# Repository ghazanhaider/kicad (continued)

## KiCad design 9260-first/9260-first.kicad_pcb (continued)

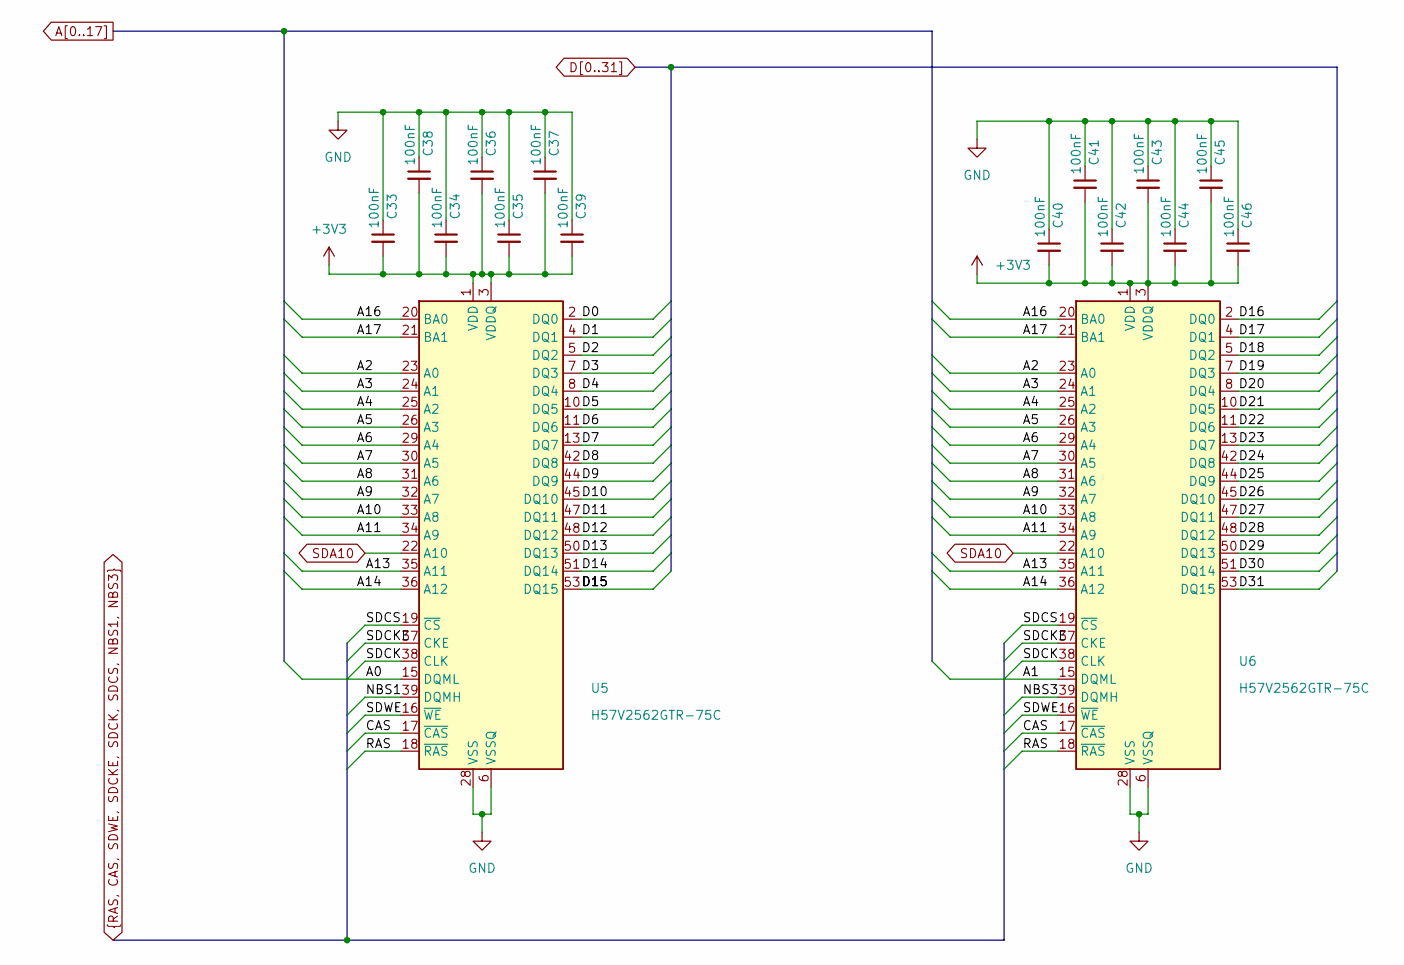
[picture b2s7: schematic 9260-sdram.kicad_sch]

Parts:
C33, C34, C35, C36, C37, C38, C39, C40, C41, C42, C43, C44, C45, C46: 100nF; C_0805_2012Metric
U5, U6: H57V2562GTR-75C; TSOP-II-54_22.2x10.16mm_P0.8mm

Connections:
3V3: C33.2, C34.2, C35.2, C36.2, C37.2, C38.2, C39.2, C40.2, C41.2, C42.2, C43.2, C44.2, C45.2, C46.2, U5.1 (VDD), U5.3 (VDDQ), U5.9 (VDDQ), U5.14 (VDD), U5.27 (VDD), U5.43 (VDDQ), U5.49 (VDDQ), U6.1 (VDD), U6.3 (VDDQ), U6.9 (VDDQ), U6.14 (VDD), U6.27 (VDD), U6.43 (VDDQ), U6.49 (VDDQ); also elsewhere on the board
A0: U5.15 (DQML); also elsewhere on the board
A1: U6.15 (DQML); also elsewhere on the board
A2: U5.23 (A0), U6.23 (A0); also elsewhere on the board
A3: U5.24 (A1), U6.24 (A1); also elsewhere on the board
A4: U5.25 (A2), U6.25 (A2); also elsewhere on the board
A5: U5.26 (A3), U6.26 (A3); also elsewhere on the board
A6: U5.29 (A4), U6.29 (A4); also elsewhere on the board
A7: U5.30 (A5), U6.30 (A5); also elsewhere on the board
A8: U5.31 (A6), U6.31 (A6); also elsewhere on the board
A9: U5.32 (A7), U6.32 (A7); also elsewhere on the board
A10: U5.33 (A8), U6.33 (A8); also elsewhere on the board
A11: U5.34 (A9), U6.34 (A9); also elsewhere on the board
A13: U5.35 (A11), U6.35 (A11); also elsewhere on the board
A14: U5.36 (A12), U6.36 (A12); also elsewhere on the board
A16: U5.20 (BA0), U6.20 (BA0); also elsewhere on the board
A17: U5.21 (BA1), U6.21 (BA1); also elsewhere on the board
CAS: U5.17 (~CAS), U6.17 (~CAS); also elsewhere on the board
D0: U5.2 (DQ0); also elsewhere on the board
D1: U5.4 (DQ1); also elsewhere on the board
D2: U5.5 (DQ2); also elsewhere on the board
D3: U5.7 (DQ3); also elsewhere on the board
D4: U5.8 (DQ4); also elsewhere on the board
D5: U5.10 (DQ5); also elsewhere on the board
D6: U5.11 (DQ6); also elsewhere on the board
D7: U5.13 (DQ7); also elsewhere on the board
D8: U5.42 (DQ8); also elsewhere on the board
D9: U5.44 (DQ9); also elsewhere on the board
D10: U5.45 (DQ10); also elsewhere on the board
D11: U5.47 (DQ11); also elsewhere on the board
D12: U5.48 (DQ12); also elsewhere on the board
D13: U5.50 (DQ13); also elsewhere on the board
D14: U5.51 (DQ14); also elsewhere on the board
D15: U5.53 (DQ15); also elsewhere on the board
D16: U6.2 (DQ0); also elsewhere on the board
D17: U6.4 (DQ1); also elsewhere on the board
D18: U6.5 (DQ2); also elsewhere on the board
D19: U6.7 (DQ3); also elsewhere on the board
D20: U6.8 (DQ4); also elsewhere on the board
D21: U6.10 (DQ5); also elsewhere on the board
D22: U6.11 (DQ6); also elsewhere on the board
D23: U6.13 (DQ7); also elsewhere on the board
D24: U6.42 (DQ8); also elsewhere on the board
D25: U6.44 (DQ9); also elsewhere on the board
D26: U6.45 (DQ10); also elsewhere on the board
D27: U6.47 (DQ11); also elsewhere on the board
D28: U6.48 (DQ12); also elsewhere on the board
D29: U6.50 (DQ13); also elsewhere on the board
D30: U6.51 (DQ14); also elsewhere on the board
D31: U6.53 (DQ15); also elsewhere on the board
GND: C33.1, C34.1, C35.1, C36.1, C37.1, C38.1, C39.1, C40.1, C41.1, C42.1, C43.1, C44.1, C45.1, C46.1, U5.6 (VSSQ), U5.12 (VSSQ), U5.28 (VSS), U5.41 (VSS), U5.46 (VSSQ), U5.52 (VSSQ), U5.54 (VSS), U6.6 (VSSQ), U6.12 (VSSQ), U6.28 (VSS), U6.41 (VSS), U6.46 (VSSQ), U6.52 (VSSQ), U6.54 (VSS); also elsewhere on the board
NBS1: U5.39 (DQMH); also elsewhere on the board
NBS3: U6.39 (DQMH); also elsewhere on the board
RAS: U5.18 (~RAS), U6.18 (~RAS); also elsewhere on the board
SDA10: U5.22 (A10), U6.22 (A10); also elsewhere on the board
SDCK: U5.38 (CLK), U6.38 (CLK); also elsewhere on the board
SDCKE: U5.37 (CKE), U6.37 (CKE); also elsewhere on the board
SDCS: U5.19 (~CS), U6.19 (~CS); also elsewhere on the board
SDWE: U5.16 (~WE), U6.16 (~WE); also elsewhere on the board

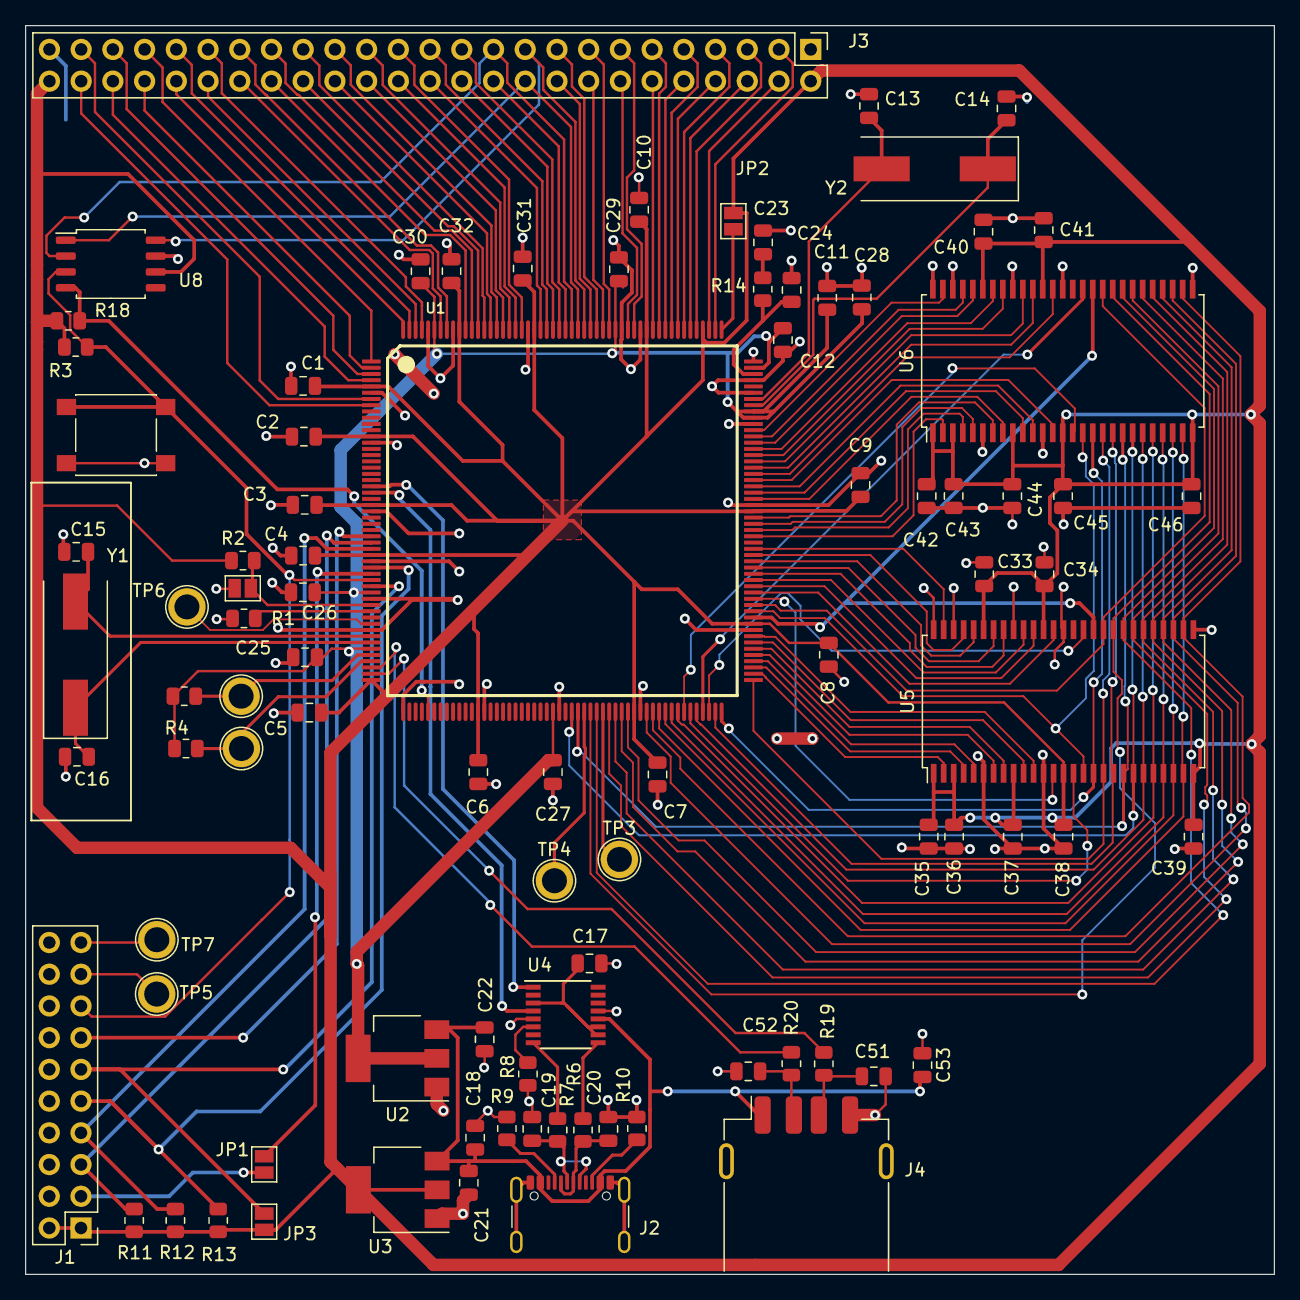
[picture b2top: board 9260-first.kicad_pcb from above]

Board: 2 copper layers, 100.0 x 100.0 mm, 91 parts (0 on the bottom side), 146 nets.

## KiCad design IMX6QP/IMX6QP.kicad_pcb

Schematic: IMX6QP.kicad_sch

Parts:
U1: MCIMX6QP5EYM; BGA-624_21x21mm_Layout25x25_P0.8mm

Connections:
GND: U1.A5 (FA_ANA), U1.B5 (VDD_FA), U1.E12 (TEST_MODE); also elsewhere on the board

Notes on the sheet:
UNUSED PINS Label overrides

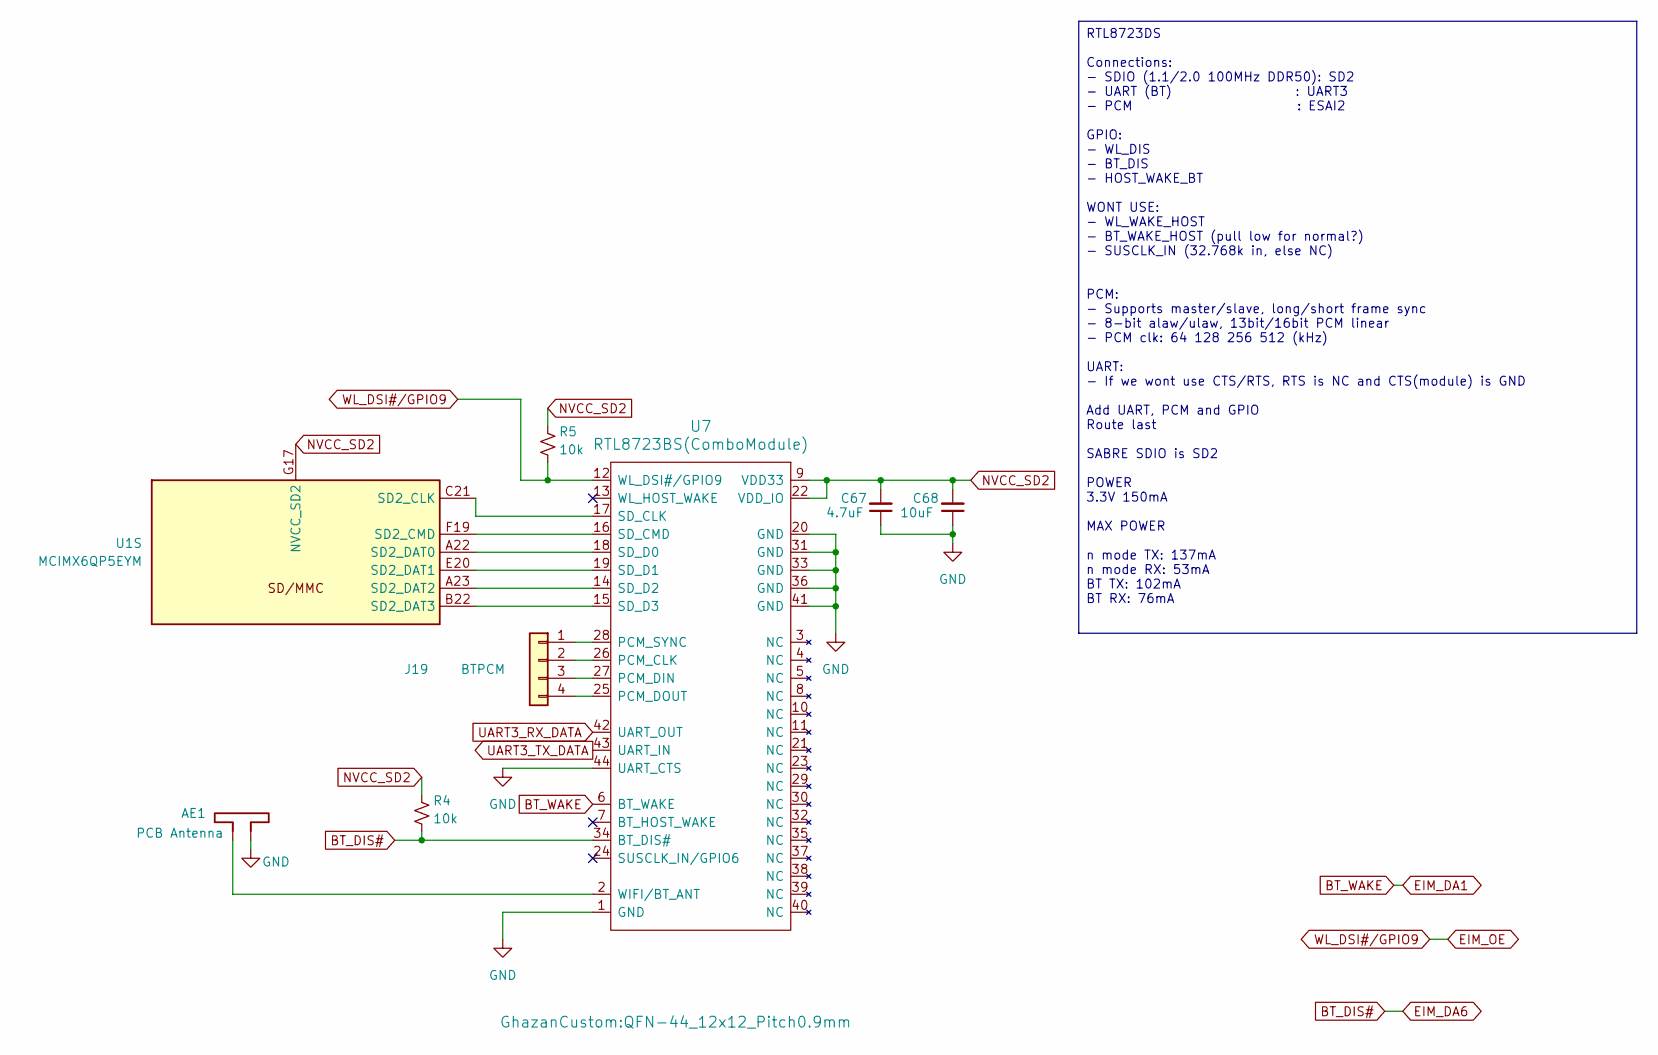
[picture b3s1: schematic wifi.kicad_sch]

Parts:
AE1: PCB Antenna; Texas_SWRA117D_2.4GHz_Left
C67: 4.7uF; C_0603_1608Metric
C68: 10uF; C_0603_1608Metric
J19: BTPCM; PinHeader_1x04_P2.54mm_Vertical
R4, R5: 10k; R_0603_1608Metric
U1: MCIMX6QP5EYM; BGA-624_21x21mm_Layout25x25_P0.8mm
U7: RTL8723BS(ComboModule); QFN-44_12x12_Pitch0.9mm

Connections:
3V3_SW2: C67.2, C68.2, R4.1, R5.1, U1.G17 (NVCC_SD2), U7.9 (VDD33), U7.22 (VDD_IO); also elsewhere on the board
BT_DIS#: R4.2, U7.34 (BT_DIS#); also elsewhere on the board
BT_WAKE: U7.6 (BT_WAKE); also elsewhere on the board
EIM_OE: R5.2, U7.12 (WL_DSI#/GPIO9); also elsewhere on the board
GND: AE1.2, C67.1, C68.1, U7.1 (GND), U7.20 (GND), U7.31 (GND), U7.33 (GND), U7.36 (GND), U7.41 (GND), U7.44 (UART_CTS); also elsewhere on the board
unnamed: J19.1, U7.28 (PCM_SYNC)
unnamed: J19.2, U7.26 (PCM_CLK)
unnamed: J19.3, U7.27 (PCM_DIN)
unnamed: J19.4, U7.25 (PCM_DOUT)
unnamed: U1.C21 (SD2_CLK), U7.17 (SD_CLK)
unnamed: U1.F19 (SD2_CMD), U7.16 (SD_CMD)
unnamed: U1.A22 (SD2_DAT0), U7.18 (SD_D0)
unnamed: U1.E20 (SD2_DAT1), U7.19 (SD_D1)
unnamed: U1.A23 (SD2_DAT2), U7.14 (SD_D2)
unnamed: U1.B22 (SD2_DAT3), U7.15 (SD_D3)
unnamed: AE1.1, U7.2 (WIFI/BT_ANT)
UART3_RX_DATA: U7.42 (UART_OUT); also elsewhere on the board
UART3_TX_DATA: U7.43 (UART_IN); also elsewhere on the board

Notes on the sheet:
RTL8723DS Connections: - SDIO (1.1/2.0 100MHz DDR50): SD2 - UART (BT) : UART3 - PCM : ESAI2 GPIO: - WL_DIS - BT_DIS - HOST_WAKE_BT WONT USE: - WL_WAKE_HOST - BT_WAKE_HOST (pull low for normal?) - SUSCLK_IN (32.768k in, else NC) PCM: - Supports master/slave, long/short frame sync - 8-bit alaw/ulaw, 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

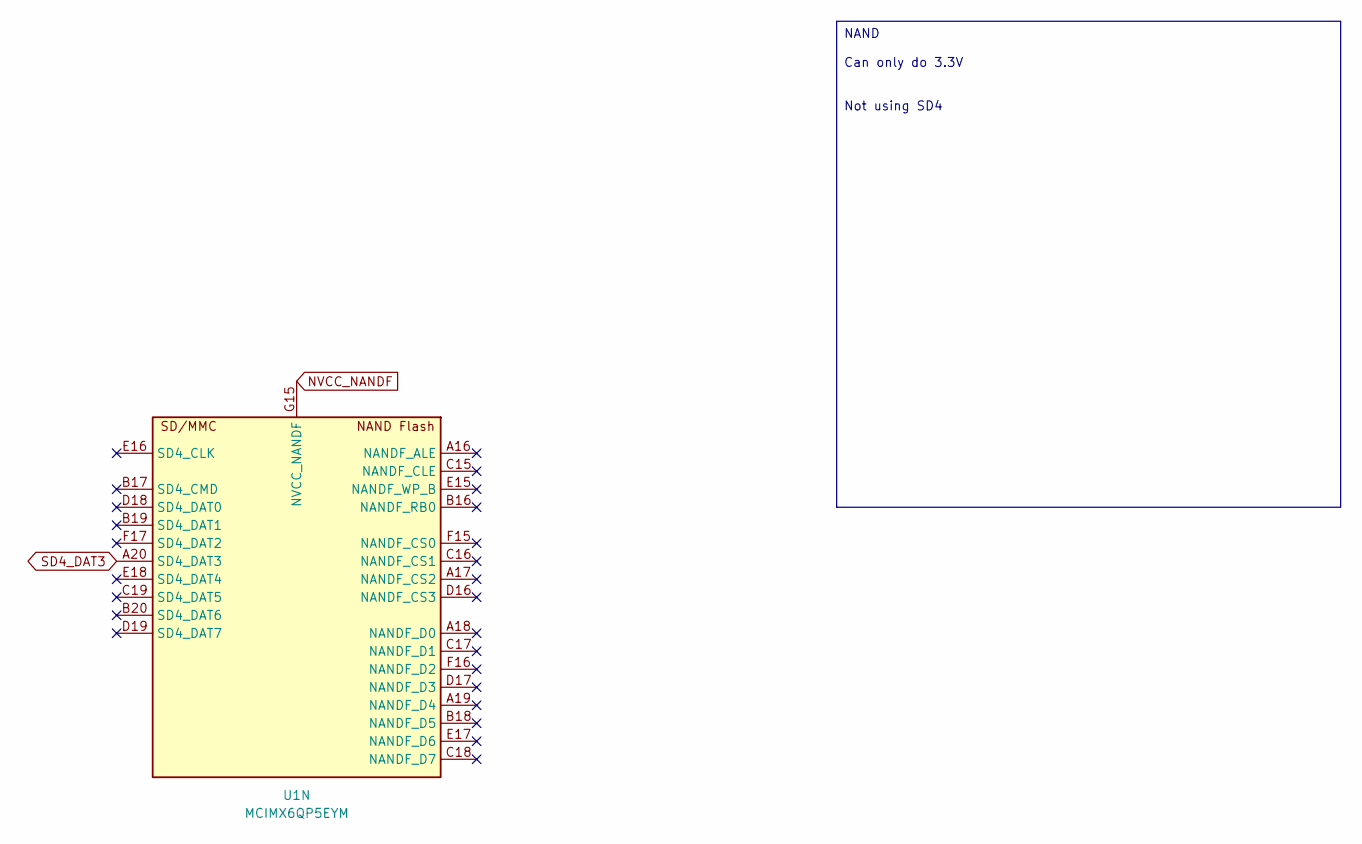
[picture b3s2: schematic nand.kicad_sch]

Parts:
U1: MCIMX6QP5EYM; BGA-624_21x21mm_Layout25x25_P0.8mm

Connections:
3V3_SW2: U1.G15 (NVCC_NANDF); also elsewhere on the board
SD1_CD: U1.A20 (SD4_DAT3); also elsewhere on the board

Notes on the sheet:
NAND Can only do 3.3V Not using SD4

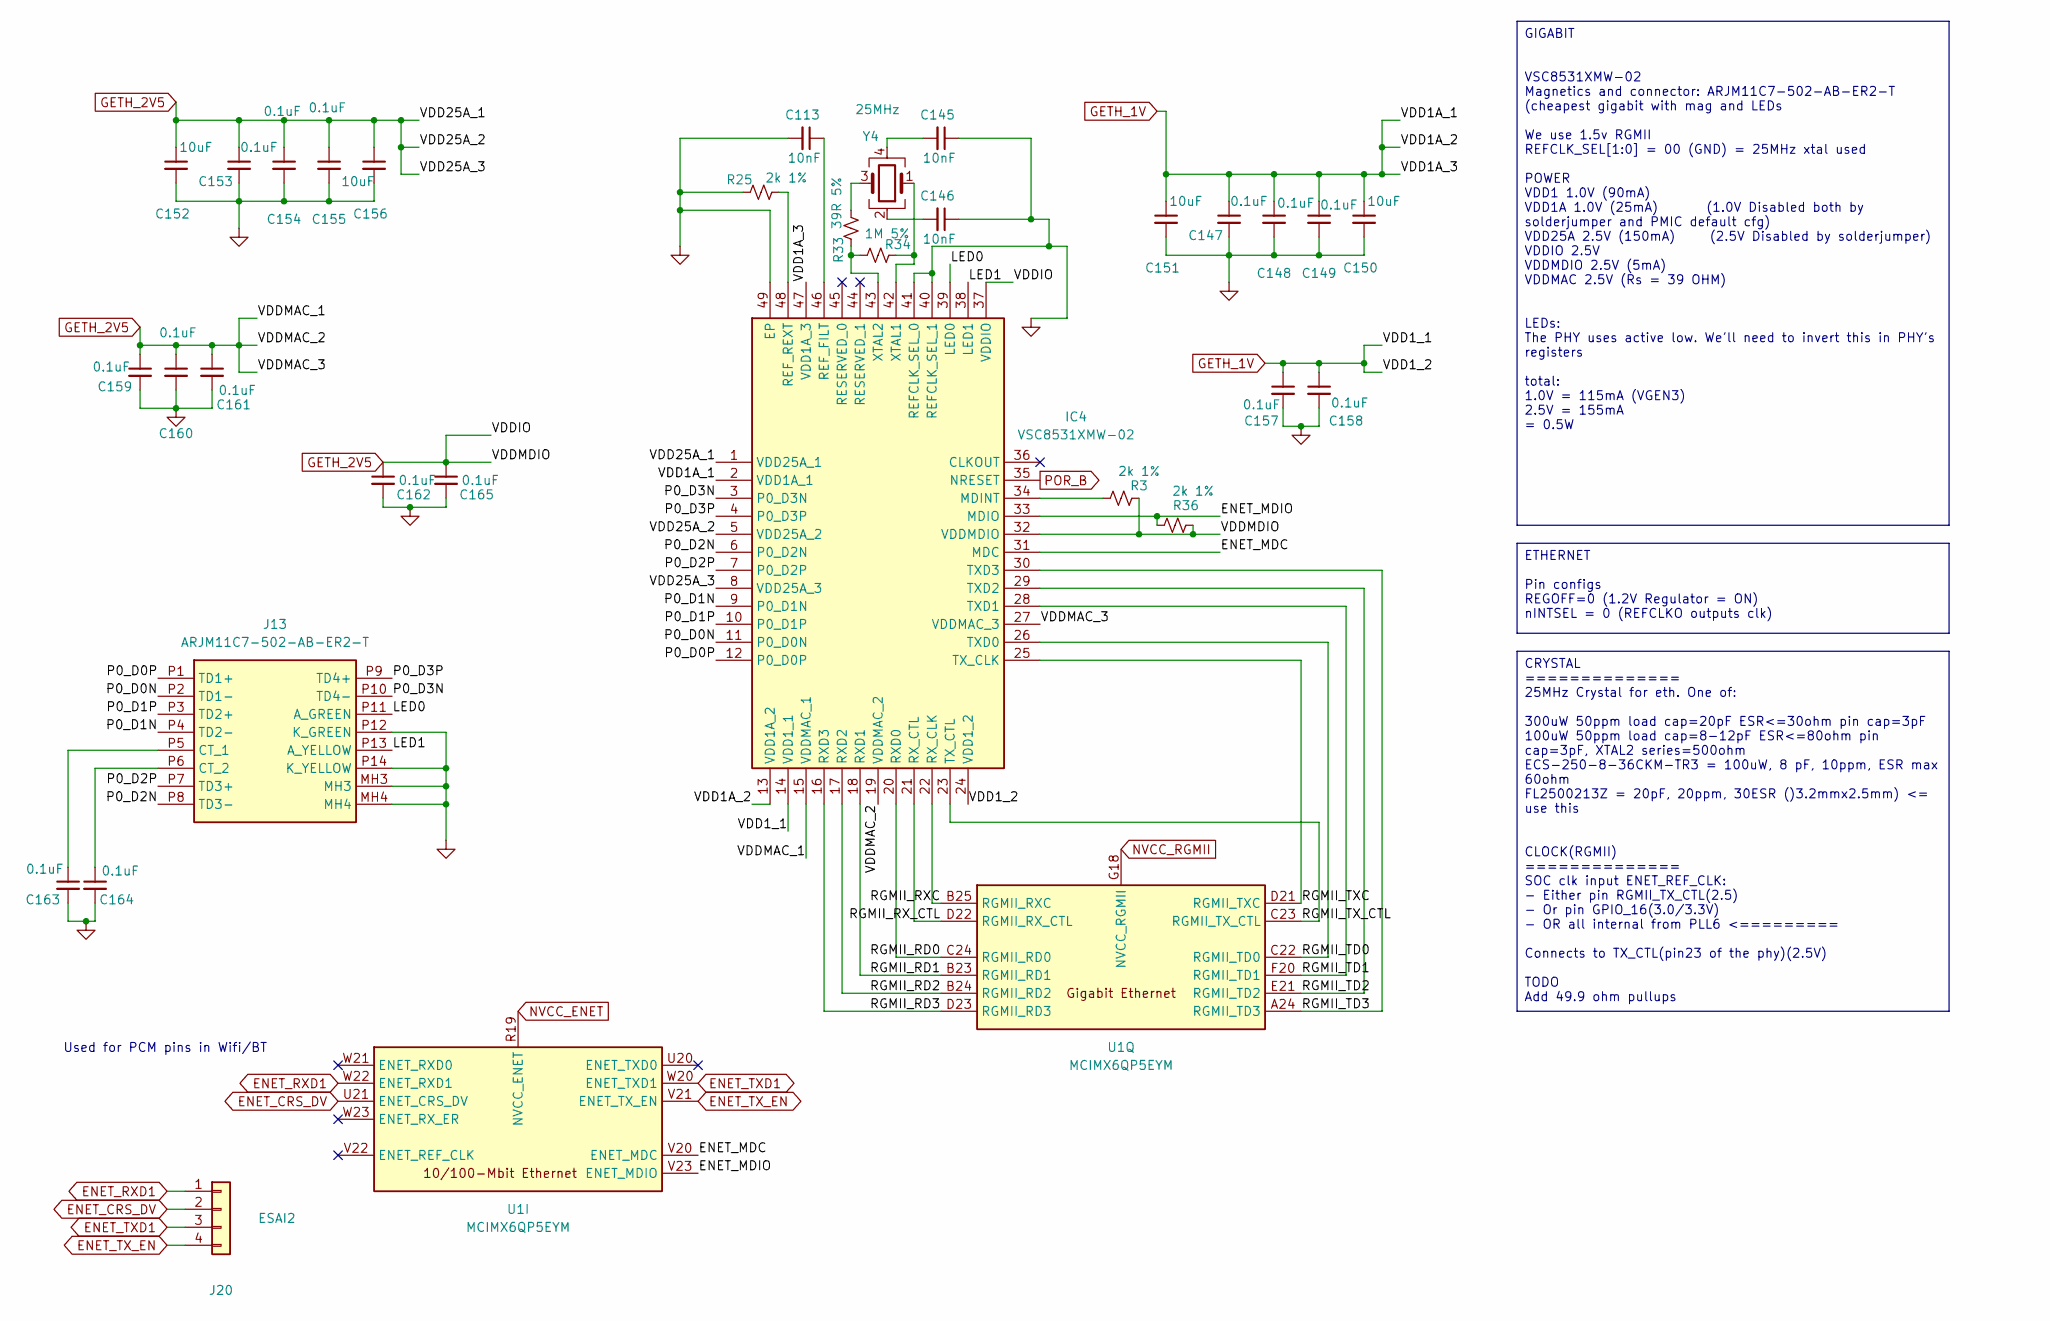
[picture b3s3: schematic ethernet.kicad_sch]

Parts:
C113, C145, C146: 10nF; C_0603_1608Metric
C147, C148, C149, C153, C154, C155, C157, C158, C159, C160, C161, C162, C163, C164, C165: 0.1uF; C_0603_1608Metric
C150, C151, C152, C156: 10uF; C_0603_1608Metric
IC4: VSC8531XMW-02; QFN40P600X600X90-49N-D; Mouser Part Number 494-VSC8531XMW-02
J13: ARJM11C7-502-AB-ER2-T; ARJM11C7502ABER2T; Mouser Part Number 815-RJM11C7502ABER2T
J20: ESAI2; PinHeader_1x04_P2.54mm_Vertical
R3, R25, R36: 2k 1%; R_0603_1608Metric
R33: 39R 5%; R_0603_1608Metric
R34: 1M 5%; R_0603_1608Metric
U1: MCIMX6QP5EYM; BGA-624_21x21mm_Layout25x25_P0.8mm
Y4: 25MHz; Crystal_SMD_3225-4Pin_3.2x2.5mm

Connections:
1V5_SW3: U1.G18 (NVCC_RGMII); also elsewhere on the board
3V3_SW2: U1.R19 (NVCC_ENET); also elsewhere on the board
/Ethernet/ENET_MDC: IC4.31 (MDC), U1.V20 (ENET_MDC)
/Ethernet/ENET_MDIO: IC4.33 (MDIO), R36.2, U1.V23 (ENET_MDIO)
/Ethernet/LED0: IC4.39 (LED0), J13.P11 (A_GREEN)
/Ethernet/LED1: IC4.38 (LED1), J13.P13 (A_YELLOW)
/Ethernet/P0_D0N: IC4.11 (P0_D0N), J13.P2 (TD1-)
/Ethernet/P0_D0P: IC4.12 (P0_D0P), J13.P1 (TD1+)
/Ethernet/P0_D1N: IC4.9 (P0_D1N), J13.P4 (TD2-)
/Ethernet/P0_D1P: IC4.10 (P0_D1P), J13.P3 (TD2+)
/Ethernet/P0_D2N: IC4.6 (P0_D2N), J13.P8 (TD3-)
/Ethernet/P0_D2P: IC4.7 (P0_D2P), J13.P7 (TD3+)
/Ethernet/P0_D3N: IC4.3 (P0_D3N), J13.P10 (TD4-)
/Ethernet/P0_D3P: IC4.4 (P0_D3P), J13.P9 (TD4+)
/Ethernet/RGMII_RD0: IC4.20 (RXD0), U1.C24 (RGMII_RD0)
/Ethernet/RGMII_RD1: IC4.18 (RXD1), U1.B23 (RGMII_RD1)
/Ethernet/RGMII_RD2: IC4.17 (RXD2), U1.B24 (RGMII_RD2)
/Ethernet/RGMII_RD3: IC4.16 (RXD3), U1.D23 (RGMII_RD3)
/Ethernet/RGMII_RXC: IC4.22 (RX_CLK), U1.B25 (RGMII_RXC)
/Ethernet/RGMII_RX_CTL: IC4.21 (RX_CTL), U1.D22 (RGMII_RX_CTL)
/Ethernet/RGMII_TD0: IC4.26 (TXD0), U1.C22 (RGMII_TD0)
/Ethernet/RGMII_TD1: IC4.28 (TXD1), U1.F20 (RGMII_TD1)
/Ethernet/RGMII_TD2: IC4.29 (TXD2), U1.E21 (RGMII_TD2)
/Ethernet/RGMII_TD3: IC4.30 (TXD3), U1.A24 (RGMII_TD3)
/Ethernet/RGMII_TXC: IC4.25 (TX_CLK), U1.D21 (RGMII_TXC)
/Ethernet/RGMII_TX_CTL: IC4.23 (TX_CTL), U1.C23 (RGMII_TX_CTL)
ENET_CRS_DV: J20.2, U1.U21 (ENET_CRS_DV)
ENET_RXD1: J20.1, U1.W22 (ENET_RXD1)
ENET_TXD1: J20.3, U1.W20 (ENET_TXD1)
ENET_TX_EN: J20.4, U1.V21 (ENET_TX_EN)
GETH_1V: C147.1, C148.1, C149.1, C150.1, C151.1, C157.1, C158.1, IC4.2 (VDD1A_1), IC4.13 (VDD1A_2), IC4.14 (VDD1_1), IC4.24 (VDD1_2), IC4.47 (VDD1A_3); also elsewhere on the board
GETH_2V5: C152.1, C153.1, C154.1, C155.1, C156.1, C159.1, C160.1, C161.1, C162.1, C165.1, IC4.1 (VDD25A_1), IC4.5 (VDD25A_2), IC4.8 (VDD25A_3), IC4.15 (VDDMAC_1), IC4.19 (VDDMAC_2), IC4.27 (VDDMAC_3), IC4.32 (VDDMDIO), IC4.37 (VDDIO), R3.1, R36.1; also elsewhere on the board
GND: C113.2, C145.1, C146.1, C147.2, C148.2, C149.2, C150.2, C151.2, C152.2, C153.2, C154.2, C155.2, C156.2, C157.2, C158.2, C159.2, C160.2, C161.2, C162.2, C163.2, C164.2, C165.2, IC4.40 (REFCLK_SEL_1), IC4.41 (REFCLK_SEL_0), IC4.49 (EP), J13.MH3, J13.MH4, J13.P12 (K_GREEN), J13.P14 (K_YELLOW), R25.1; also elsewhere on the board
unnamed: C145.2, Y4.4
unnamed: C146.2, Y4.2
unnamed: IC4.34 (MDINT), R3.2
unnamed: C113.1, IC4.46 (REF_FILT)
unnamed: IC4.48 (REF_REXT), R25.2
unnamed: IC4.42 (XTAL1), R34.1, Y4.1
unnamed: IC4.43 (XTAL2), R33.1, R34.2
unnamed: C163.1, J13.P5 (CT_1)
unnamed: C164.1, J13.P6 (CT_2)
unnamed: R33.2, Y4.3
POR_B: IC4.35 (NRESET); also elsewhere on the board

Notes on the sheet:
Used for PCM pins in Wifi/BT
GIGABIT VSC8531XMW-02 Magnetics and connector: ARJM11C7-502-AB-ER2-T (cheapest gigabit with mag and LEDs We use 1.5v RGMII REFCLK_SEL[1:0] = 00 (GND) = 25MHz xtal used POWER VDD1 1.0V (90mA) VDD1A 1.0V (25mA) (1.0V Disabled both by solderjumper and PMIC default cfg) VDD25A 2.5V (150mA) (2.5V Disabl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
CRYSTAL ============== 25MHz Crystal for eth. One of: 300uW 50ppm load cap=20pF ESR<=30ohm pin cap=3pF 100uW 50ppm load cap=8-12pF ESR<=80ohm pin cap=3pF, XTAL2 series=500ohm ECS-250-8-36CKM-TR3 = 100uW, 8 pF, 10ppm, ESR max 60ohm FL2500213Z = 20pF, 20ppm, 30ESR ()3.2mmx2.5mm) <= use this CLOCK(RGM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
ETHERNET Pin configs REGOFF=0 (1.2V Regulator = ON) nINTSEL = 0 (REFCLKO outputs clk)

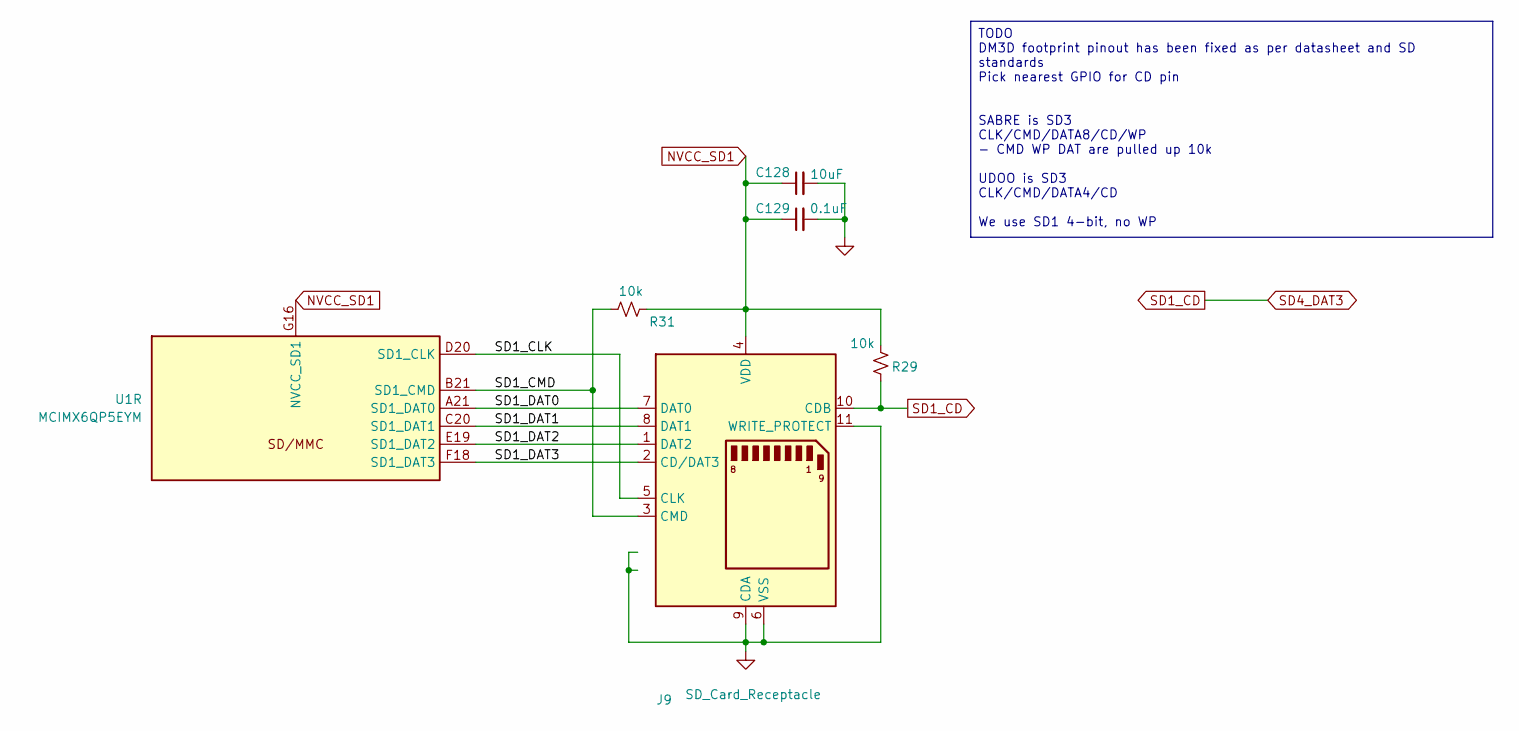
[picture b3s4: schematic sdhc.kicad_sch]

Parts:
C128: 10uF; C_0402_1005Metric
C129: 0.1uF; C_0402_1005Metric
J9: SD_Card_Receptacle; microSD_HC_Hirose_DM3D-SF
R29, R31: 10k; R_0603_1608Metric
U1: MCIMX6QP5EYM; BGA-624_21x21mm_Layout25x25_P0.8mm

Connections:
3V3_SW2: C128.1, C129.1, J9.4 (VDD), R29.2, R31.1, U1.G16 (NVCC_SD1); also elsewhere on the board
/SDHC/SD1_CLK: J9.5 (CLK), U1.D20 (SD1_CLK)
/SDHC/SD1_CMD: J9.3 (CMD), R31.2, U1.B21 (SD1_CMD)
/SDHC/SD1_DAT0: J9.7 (DAT0), U1.A21 (SD1_DAT0)
/SDHC/SD1_DAT1: J9.8 (DAT1), U1.C20 (SD1_DAT1)
/SDHC/SD1_DAT2: J9.1 (DAT2), U1.E19 (SD1_DAT2)
/SDHC/SD1_DAT3: J9.2 (CD/DAT3), U1.F18 (SD1_DAT3)
GND: C128.2, C129.2, J9.6 (VSS), J9.9 (CDA), J9.11 (WRITE_PROTECT); also elsewhere on the board
SD1_CD: J9.10 (CDB), R29.1; also elsewhere on the board

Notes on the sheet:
TODO DM3D footprint pinout has been fixed as per datasheet and SD standards Pick nearest GPIO for CD pin SABRE is SD3 CLK/CMD/DATA8/CD/WP - CMD WP DAT are pulled up 10k UDOO is SD3 CLK/CMD/DATA4/CD We use SD1 4-bit, no WP

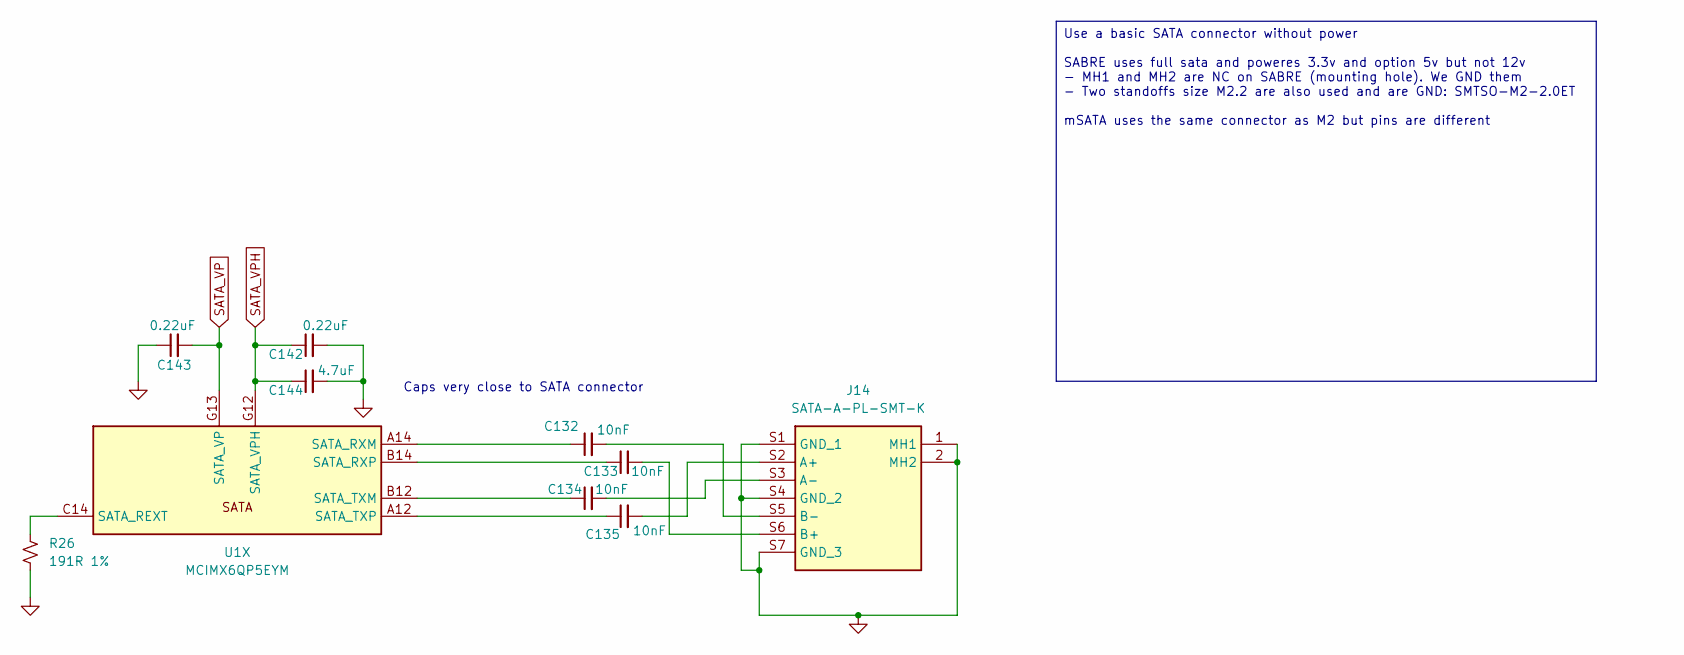
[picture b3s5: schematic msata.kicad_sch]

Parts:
C132, C133, C134, C135: 10nF; C_0603_1608Metric
C142, C143: 0.22uF; C_0402_1005Metric
C144: 4.7uF; C_0603_1608Metric
J14: SATA-A-PL-SMT-K; SATAAPLSMTK; Mouser Part Number 737-SATA-A-PL-SMT-K
R26: 191R 1%; R_0603_1608Metric
U1: MCIMX6QP5EYM; BGA-624_21x21mm_Layout25x25_P0.8mm

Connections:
GND: C142.2, C143.1, C144.2, J14.1 (MH1), J14.2 (MH2), J14.S1 (GND_1), J14.S4 (GND_2), J14.S7 (GND_3), R26.2; also elsewhere on the board
HDMI_VP: C143.2, U1.G13 (SATA_VP); also elsewhere on the board
HDMI_VPH: C142.1, C144.1, U1.G12 (SATA_VPH); also elsewhere on the board
unnamed: C135.2, J14.S2 (A+)
unnamed: C134.2, J14.S3 (A-)
unnamed: C133.2, J14.S6 (B+)
unnamed: C132.2, J14.S5 (B-)
unnamed: R26.1, U1.C14 (SATA_REXT)
unnamed: C132.1, U1.A14 (SATA_RXM)
unnamed: C133.1, U1.B14 (SATA_RXP)
unnamed: C134.1, U1.B12 (SATA_TXM)
unnamed: C135.1, U1.A12 (SATA_TXP)

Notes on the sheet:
Caps very close to SATA connector
Use a basic SATA connector without power SABRE uses full sata and poweres 3.3v and option 5v but not 12v - MH1 and MH2 are NC on SABRE (mounting hole). We GND them - Two standoffs size M2.2 are also used and are GND: SMTSO-M2-2.0ET mSATA uses the same connector as M2 but pins are different

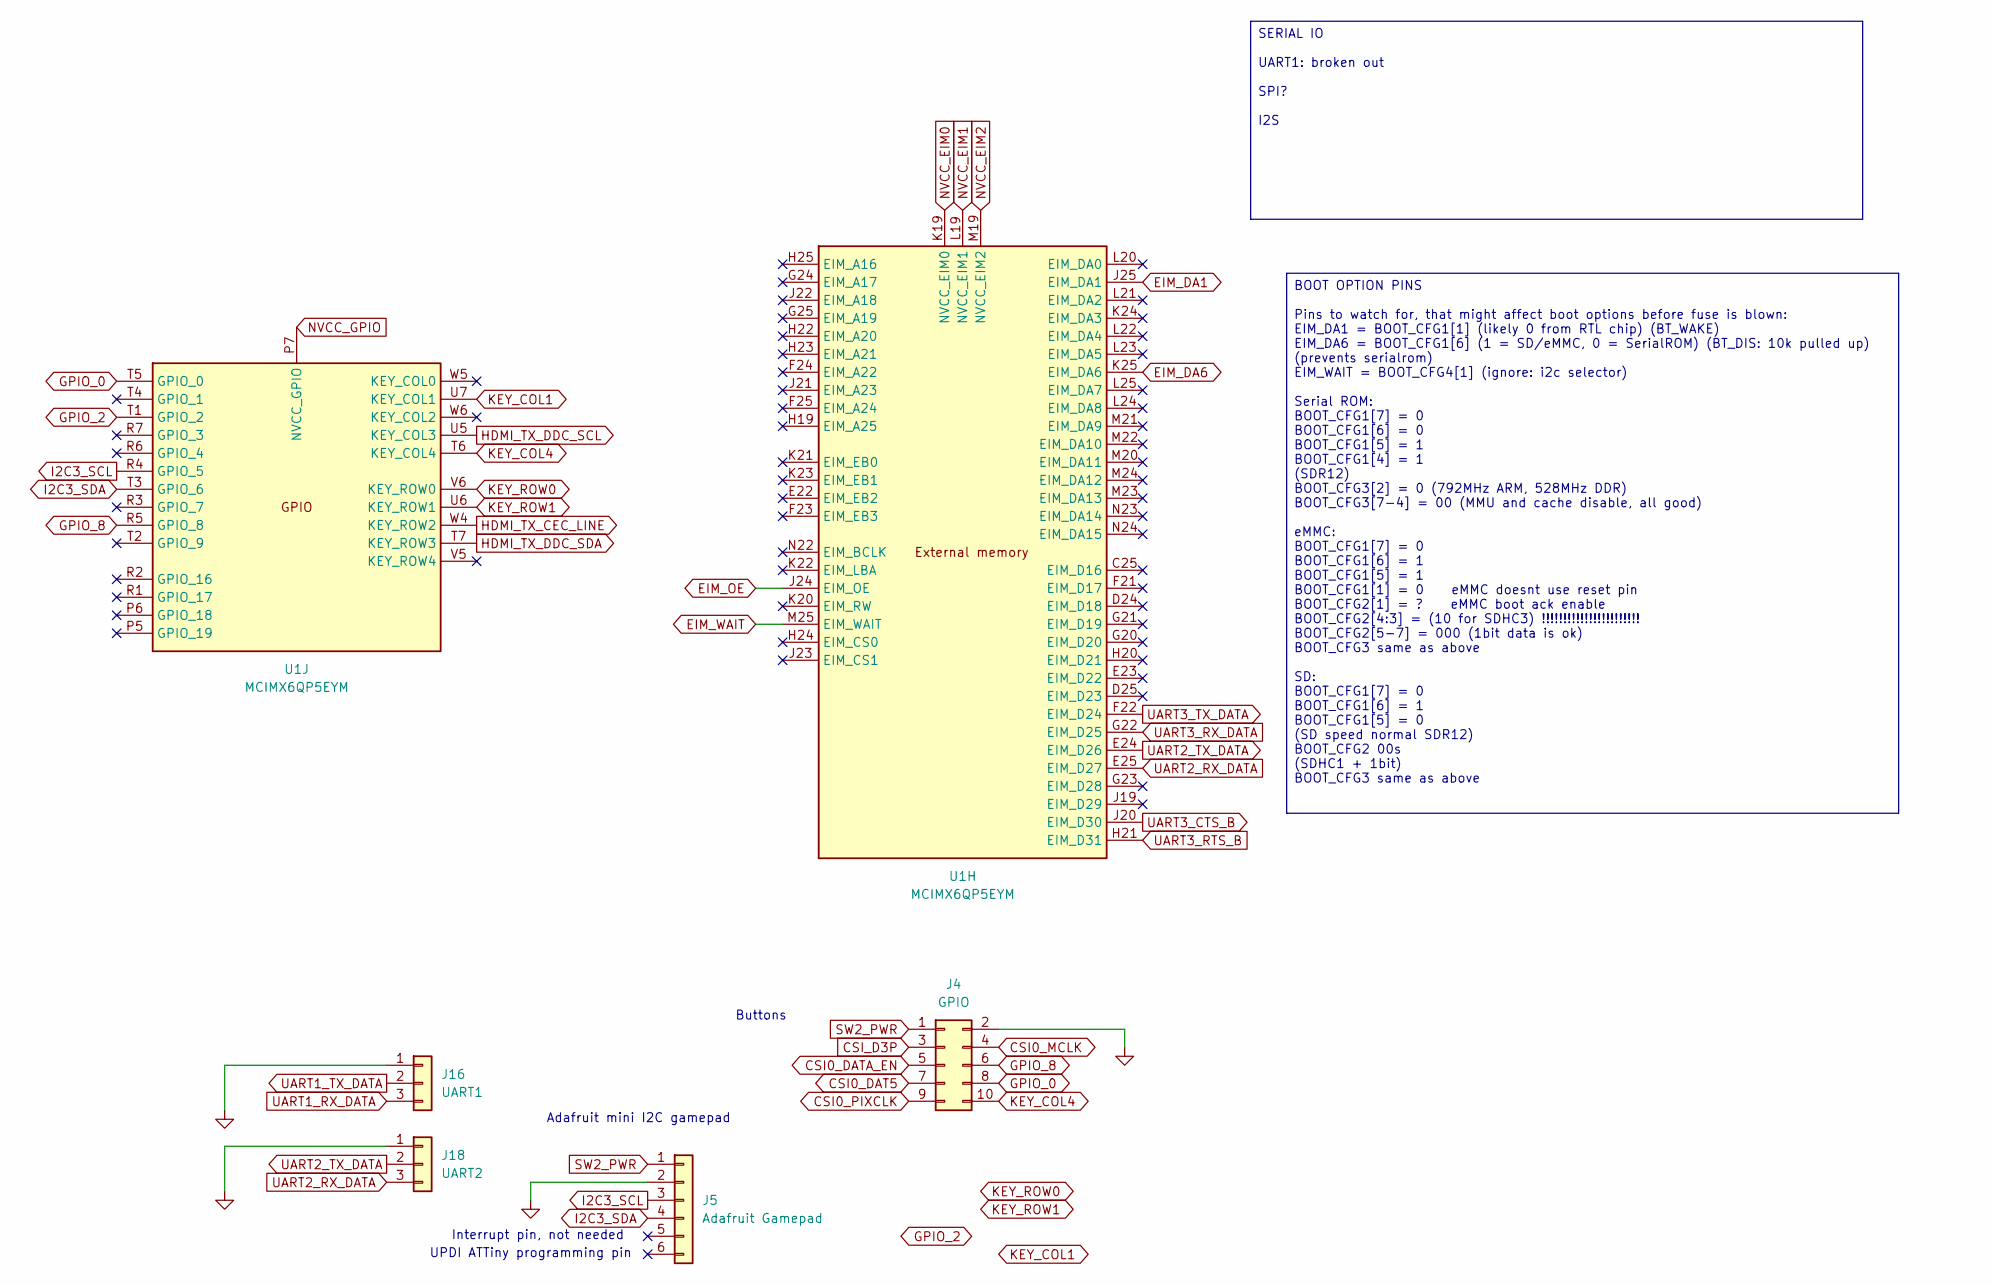
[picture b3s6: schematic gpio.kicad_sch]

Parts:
J4: GPIO; PinHeader_2x05_P2.54mm_Vertical
J5: Adafruit Gamepad; PinHeader_1x06_P2.54mm_Vertical
J16: UART1; PinHeader_1x03_P2.54mm_Vertical
J18: UART2; PinHeader_1x03_P2.54mm_Vertical
U1: MCIMX6QP5EYM; BGA-624_21x21mm_Layout25x25_P0.8mm

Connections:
3V3_SW2: J4.1, J5.1, U1.K19 (NVCC_EIM0), U1.L19 (NVCC_EIM1), U1.M19 (NVCC_EIM2), U1.P7 (NVCC_GPIO); also elsewhere on the board
BT_DIS#: U1.K25 (EIM_DA6); also elsewhere on the board
BT_WAKE: U1.J25 (EIM_DA1); also elsewhere on the board
CSI0_DAT5: J4.7; also elsewhere on the board
CSI0_DATA_EN: J4.5; also elsewhere on the board
CSI0_MCLK: J4.4; also elsewhere on the board
CSI0_PIXCLK: J4.9; also elsewhere on the board
CSI_D3P: J4.3; also elsewhere on the board
EIM_OE: U1.J24 (EIM_OE); also elsewhere on the board
EIM_WAIT: U1.M25 (EIM_WAIT); also elsewhere on the board
GND: J4.2, J5.2, J16.1, J18.1; also elsewhere on the board
GPIO_0: J4.8, U1.T5 (GPIO_0)
GPIO_2: U1.T1 (GPIO_2)
GPIO_8: J4.6, U1.R5 (GPIO_8)
HDMI_TX_CEC_LINE: U1.W4 (KEY_ROW2); also elsewhere on the board
HDMI_TX_DDC_SCL: U1.U5 (KEY_COL3); also elsewhere on the board
HDMI_TX_DDC_SDA: U1.T7 (KEY_ROW3); also elsewhere on the board
I2C3_SCL: J5.3, U1.R4 (GPIO_5)
I2C3_SDA: J5.4, U1.T3 (GPIO_6)
KEY_COL1: U1.U7 (KEY_COL1)
KEY_COL4: J4.10, U1.T6 (KEY_COL4)
KEY_ROW0: U1.V6 (KEY_ROW0)
KEY_ROW1: U1.U6 (KEY_ROW1)
UART1_RX_DATA: J16.3; also elsewhere on the board
UART1_TX_DATA: J16.2; also elsewhere on the board
UART2_RX_DATA: J18.3, U1.E25 (EIM_D27)
UART2_TX_DATA: J18.2, U1.E24 (EIM_D26)
UART3_CTS_B: U1.J20 (EIM_D30)
UART3_RTS_B: U1.H21 (EIM_D31)
UART3_RX_DATA: U1.G22 (EIM_D25); also elsewhere on the board
UART3_TX_DATA: U1.F22 (EIM_D24); also elsewhere on the board

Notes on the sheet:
Adafruit mini I2C gamepad
UPDI ATTiny programming pin
Buttons
Interrupt pin, not needed
SERIAL IO UART1: broken out SPI? I2S
BOOT OPTION PINS Pins to watch for, that might affect boot options before fuse is blown: EIM_DA1 = BOOT_CFG1[1] (likely 0 from RTL chip) (BT_WAKE) EIM_DA6 = BOOT_CFG1[6] (1 = SD/eMMC, 0 = SerialROM) (BT_DIS: 10k pulled up) (prevents serialrom) EIM_WAIT = BOOT_CFG4[1] (ignore: i2c selector) Serial R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
